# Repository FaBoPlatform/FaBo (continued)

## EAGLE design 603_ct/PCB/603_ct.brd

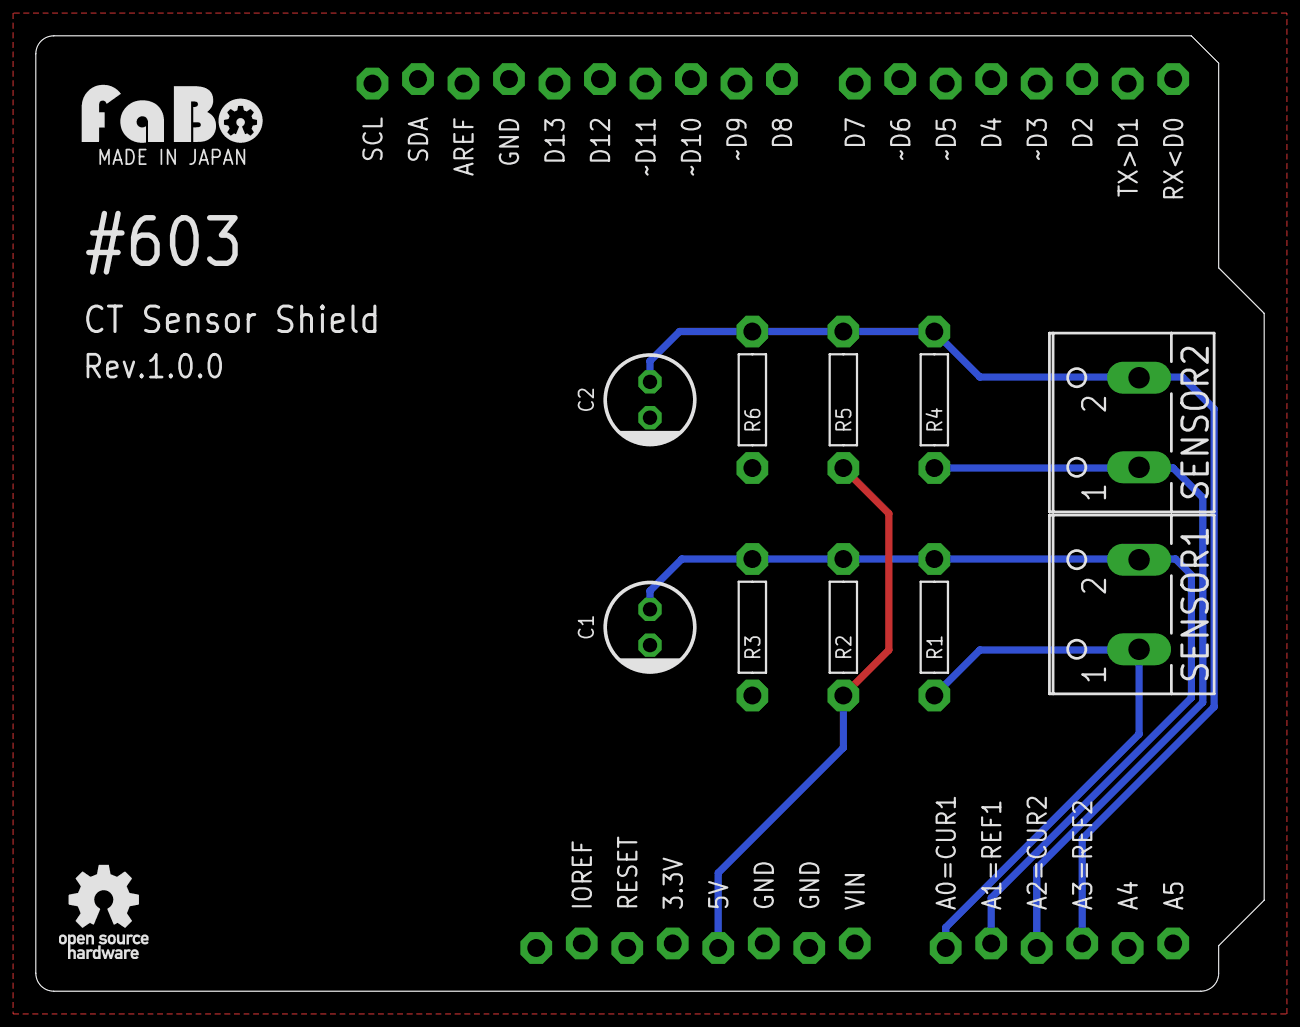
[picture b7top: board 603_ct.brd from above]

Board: 2 copper layers, 68.6 x 53.3 mm, 13 parts (0 on the bottom side), 6 nets.

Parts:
C1, C2: 10uF; CAP-POL-AXL-5MM
R1, R4: 100; RES-AXL-REGULAR
R2, R3, R5, R6: 100k; RES-AXL-REGULAR
U2: ARDUINO_UNO_R3_NOLABEL
U$2: LOGO_OSHW_T_MS
U$3: LOGO_FABO_MS
X1, X2: W237-102

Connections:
5V: R2.P$2, R5.P$2, U2.5V
CUR1: R1.P$2, U2.A0, X1.1
CUR2: R4.P$2, U2.A2, X2.1
GND: C1.-, C2.-, R3.P$1, R6.P$1, U2.GND1, U2.GND2, U2.GND3
REF1: C1.+, R1.P$1, R2.P$1, R3.P$2, U2.A1, X1.2
REF2: C2.+, R4.P$1, R5.P$1, R6.P$2, U2.A3, X2.2
